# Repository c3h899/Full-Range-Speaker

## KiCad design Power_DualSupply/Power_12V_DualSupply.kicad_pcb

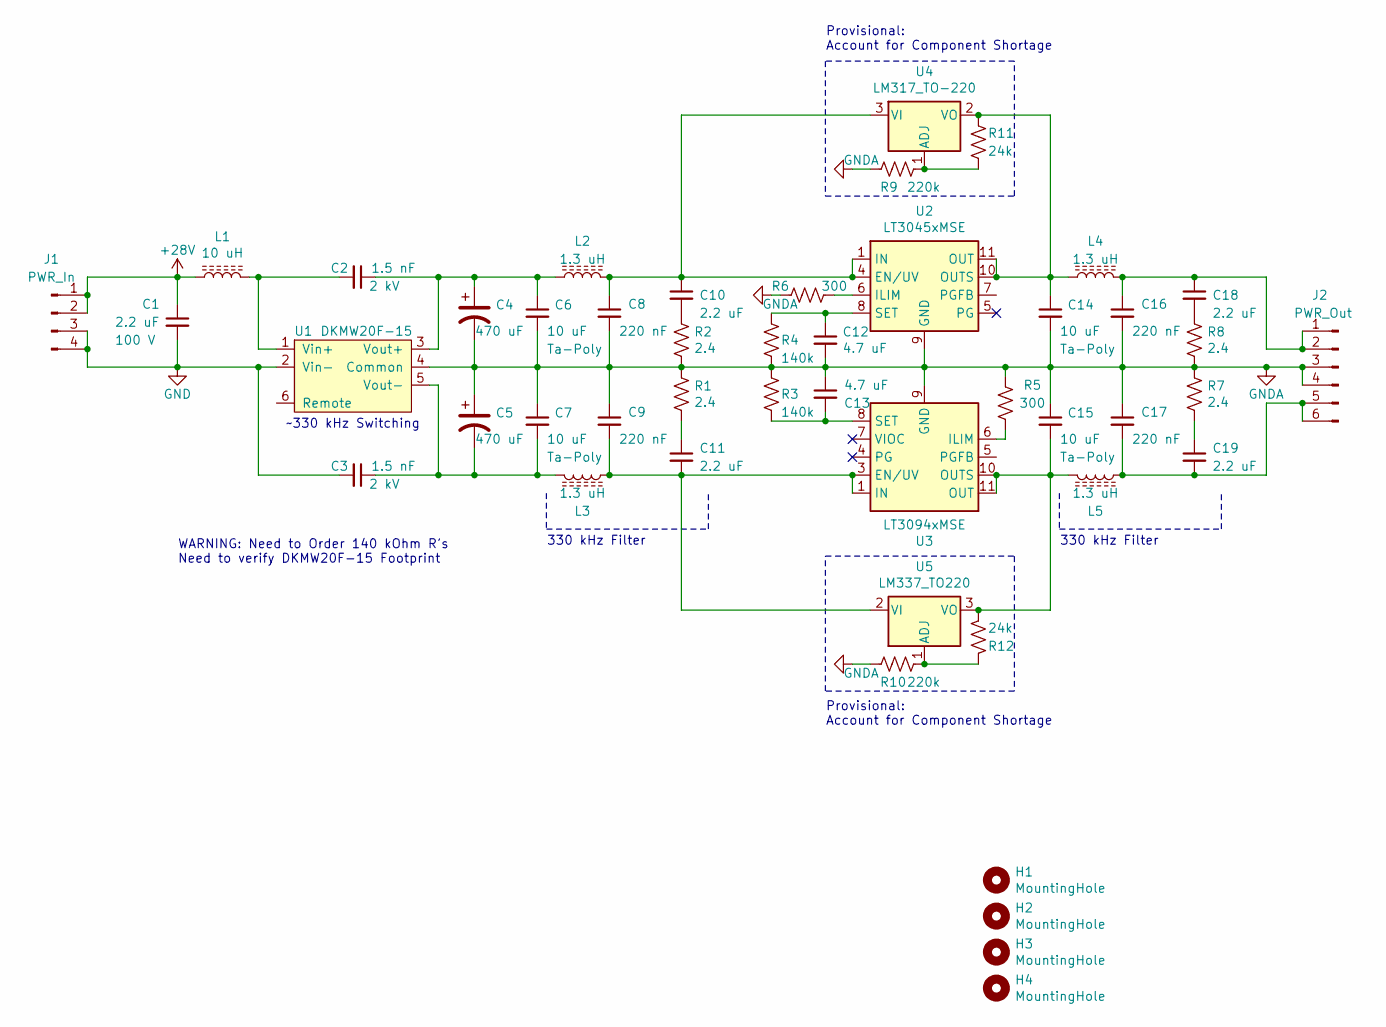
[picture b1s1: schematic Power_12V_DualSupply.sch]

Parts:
C1: 2.2 uF; C_6054; Rating 100 V; Part SMDID04220YA00KT00
C2, C3: 1.5 nF; C_1206_3216Metric_Pad1.33x1.80mm_HandSolder; Rating 2 kV; Part 1206GC152MAZ2A
C4, C5: 470 uF; CP_Radial_D10.0mm_P5.00mm; Part ESC477M035AH4AA
C6, C7, C14, C15: 10 uF; 2917_(7343_Metric)_D; Rating 50 V; Part TCJD106M050R0120
C8, C9, C16, C17: 220 nF; C_2220_5650Metric_Pad1.97x5.40mm_HandSolder; Part SMDID03220QB00MP00
C10, C11, C18, C19: 2.2 uF; C_6054; Part SMDID04220YA00KT00
C12, C13: 4.7 uF; C_1206_3216Metric_Pad1.33x1.80mm_HandSolder; Part C3216X7R1H475K160AC
H1, H2, H3, H4: MountingHole; MountingHole_3.2mm_M3_Pad_TopBottom
J1: PWR_In; PinHeader_1x04_P2.54mm_Vertical
J2: PWR_Out; PinHeader_1x06_P2.54mm_Vertical
L1: 10 uH; L_Wuerth_WE-PD-Typ-LS_Handsoldering; Part 74477110
L2, L3, L4, L5: 1.3 uH; L_Wuerth_HCM-1390; Part 7443551130
R1, R2, R7, R8: 2.4; R_2010_5025Metric_Pad1.40x2.65mm_HandSolder; Part 35022R4FT
R3, R4: 140k; C_1206_3216Metric_Pad1.33x1.80mm_HandSolder; Part RQ73C2B140KBTD
R5, R6: 300; C_1206_3216Metric_Pad1.33x1.80mm_HandSolder; Part RMCF1206FT300R
R9, R10: 220k; R_Axial_DIN0309_L9.0mm_D3.2mm_P12.70mm_Horizontal
R11, R12: 24k; R_Axial_DIN0309_L9.0mm_D3.2mm_P12.70mm_Horizontal
U1: DKMW20F-15; Converter_DCDC_MeanWell_DKMW20
U2: LT3045xMSE; MSOP-12-1EP_3x4mm_P0.65mm_EP1.65x2.85mm
U3: LT3094xMSE; MSOP-12-1EP_3x4mm_P0.65mm_EP1.65x2.85mm
U4: LM317_TO-220; TO-220-3_Vertical
U5: LM337_TO220; TO-220-3_Vertical

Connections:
+28V: C1.1, J1.1, J1.2, L1.1
GND: C1.2, C3.2, J1.3, J1.4, U1.2 (Vin-)
GNDA: C4.2, C5.1, C6.2, C7.1, C8.2, C9.1, C12.2, C13.1, C14.2, C15.1, C16.2, C17.1, J2.3, J2.4, R1.1, R2.2, R3.2, R4.1, R5.1, R6.1, R7.1, R8.2, R9.1, R10.1, U1.4 (Common), U2.9 (GND), U2.13 (GND), U3.9 (GND)
unnamed: C2.1, C4.1, C6.1, L2.1, U1.3 (Vout+)
unnamed: C2.2, L1.2, U1.1 (Vin+)
unnamed: C3.1, C5.2, C7.2, L3.2, U1.5 (Vout-)
unnamed: C8.1, C10.1, L2.2, U2.1 (IN), U2.2 (IN), U2.3 (IN), U2.4 (EN/UV), U4.3 (VI)
unnamed: C10.2, R2.1
unnamed: C11.1, R1.2
unnamed: C9.2, C11.2, L3.1, U3.1 (IN), U3.2 (IN), U3.3 (EN/UV), U3.13 (IN), U5.2 (VI)
unnamed: C12.1, R4.2, U2.8 (SET)
unnamed: C13.2, R3.1, U3.8 (SET)
unnamed: C14.1, L4.1, R11.2, U2.10 (OUTS), U2.11 (OUT), U2.12 (OUT), U4.2 (VO)
unnamed: C15.2, L5.2, R12.1, U3.10 (OUTS), U3.11 (OUT), U3.12 (OUT), U5.3 (VO)
unnamed: C16.1, C18.1, J2.1, J2.2, L4.2
unnamed: C17.2, C19.2, J2.5, J2.6, L5.1
unnamed: C18.2, R8.1
unnamed: C19.1, R7.2
unnamed: R5.2, U3.6 (ILIM)
unnamed: R6.2, U2.6 (ILIM)
unnamed: R10.2, R12.2, U5.1 (ADJ)
unnamed: R9.2, R11.1, U4.1 (ADJ)

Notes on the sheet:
~~330 kHz Switching
330 kHz Filter
WARNING: Need to Order 140 kOhm R's Need to verify DKMW20F-15 Footprint
Provisional: Account for Component Shortage

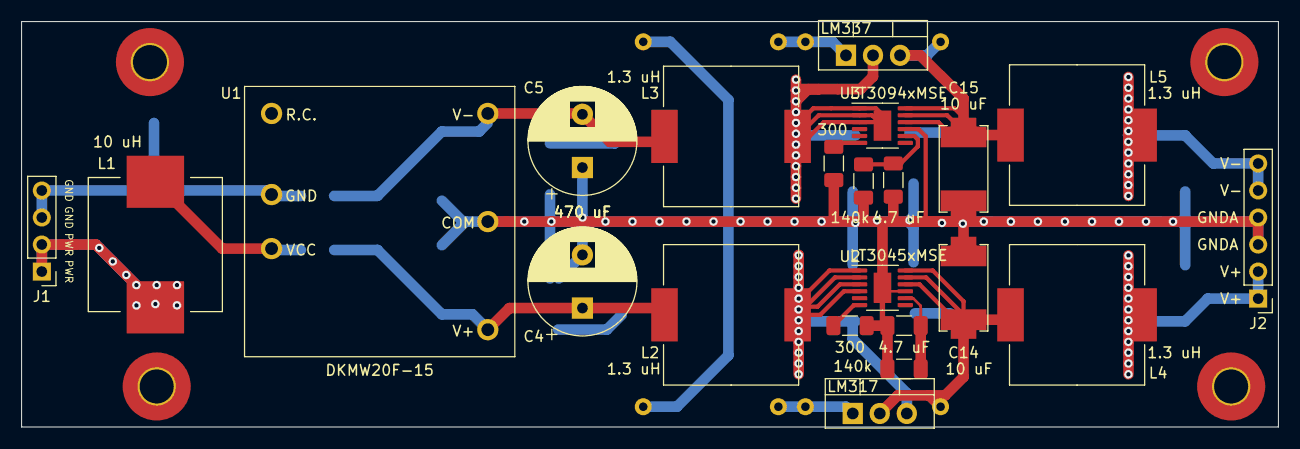
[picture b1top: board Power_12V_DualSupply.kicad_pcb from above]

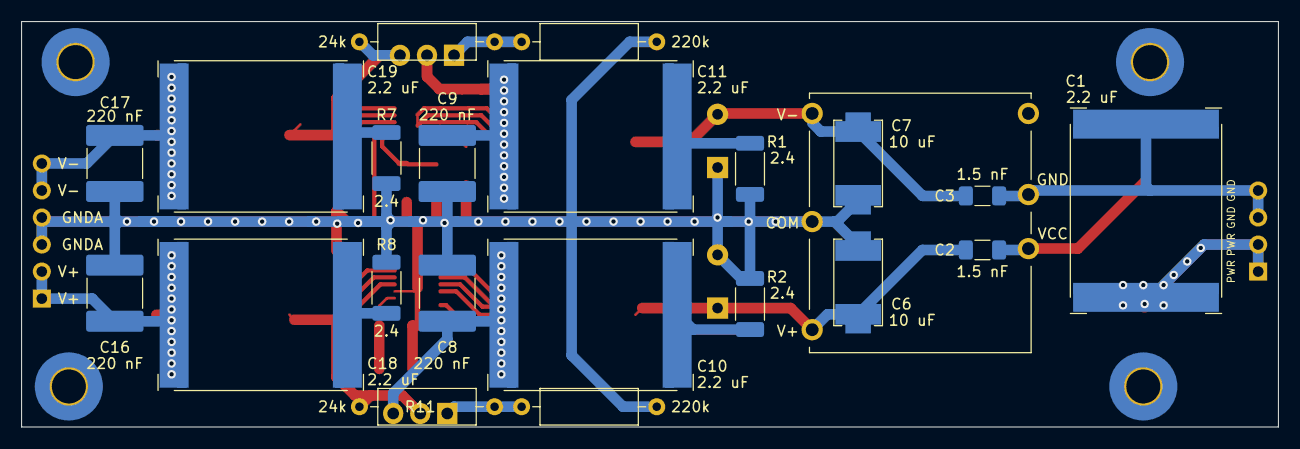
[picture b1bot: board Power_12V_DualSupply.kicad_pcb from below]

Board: 2 copper layers, 118.1 x 38.1 mm, 47 parts (21 on the bottom side), 22 nets.

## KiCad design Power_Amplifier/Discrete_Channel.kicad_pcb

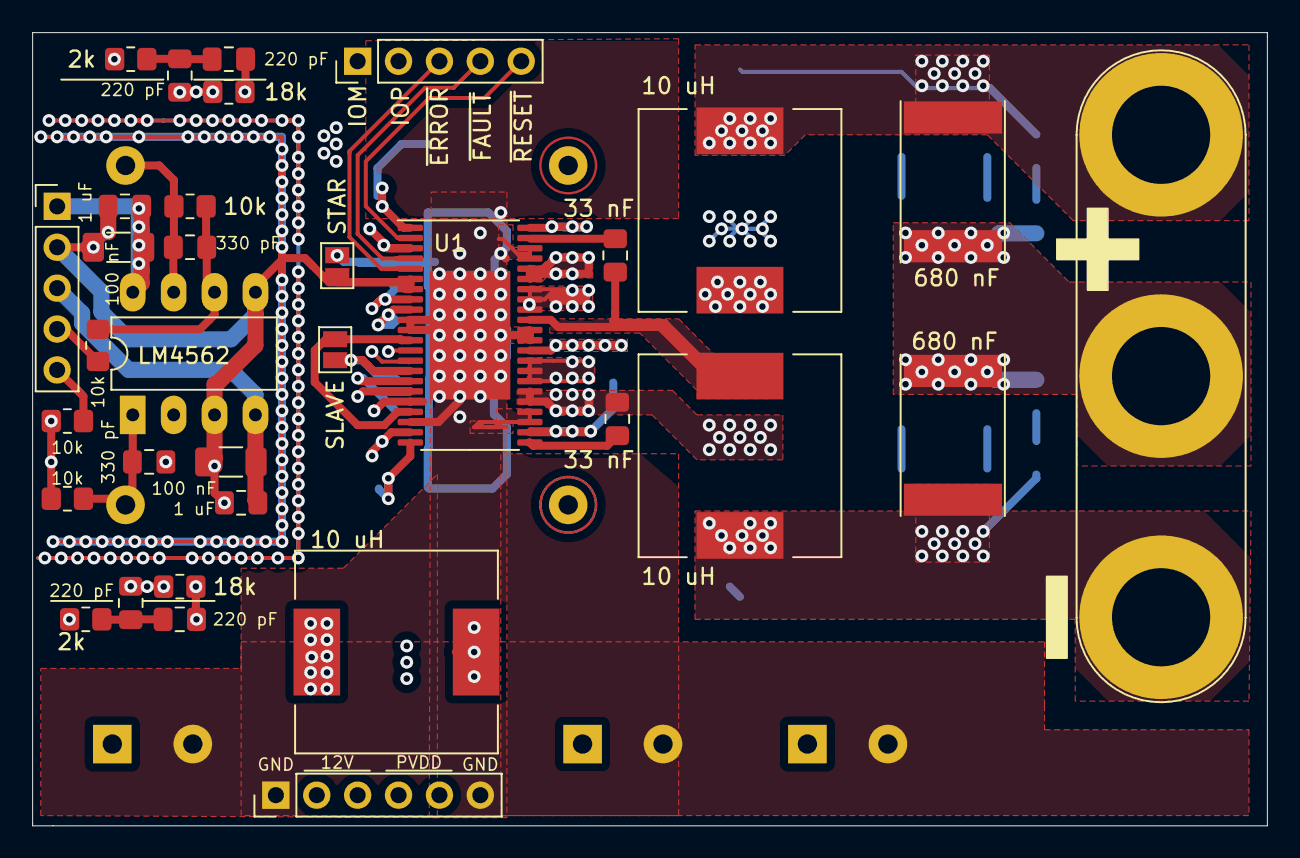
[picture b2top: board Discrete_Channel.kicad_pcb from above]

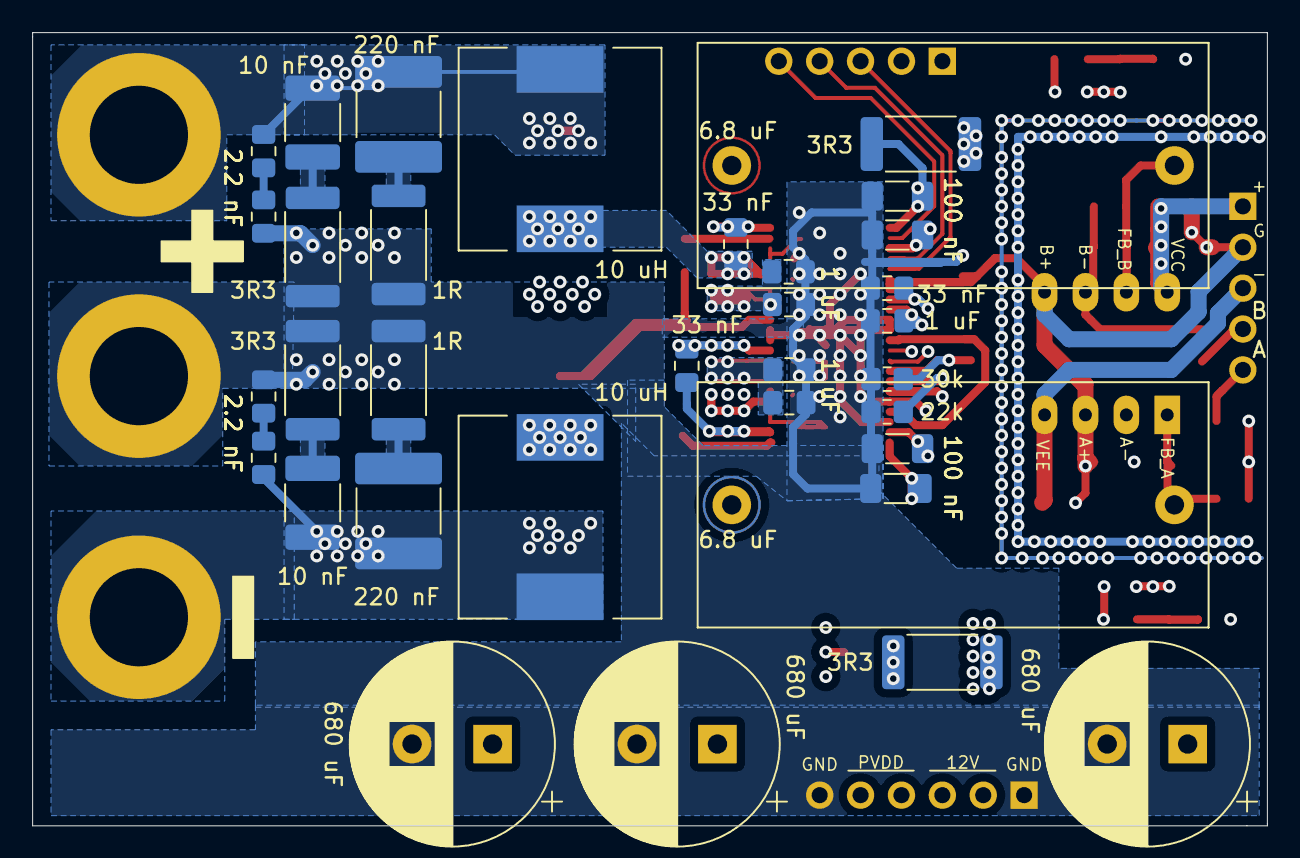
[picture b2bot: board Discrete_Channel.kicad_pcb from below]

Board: 4 copper layers, 76.7 x 49.3 mm, 68 parts (35 on the bottom side), 46 nets.

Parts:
C1, C2, C17: 680 uF; CP_Radial_D12.5mm_P5.00mm
C3, C4, C5, C7, C10, C11, C16: 1 uF; C_0805_2012Metric_Pad1.18x1.45mm_HandSolder
C6, C8, C12, C13, C14, C15: 100 nF; C_1206_3216Metric_Pad1.33x1.80mm_HandSolder
C9, C22, C23, C24, C25: 33 nF; C_0805_2012Metric_Pad1.18x1.45mm_HandSolder
C18, C19: 330 pF; C_0805_2012Metric_Pad1.18x1.45mm_HandSolder
C20, C21: 6.8 uF; C_Rect_L31.5mm_W15.0mm_P27.50mm_MKS4
C26, C27, C28, C29: 220 pF; C_0805_2012Metric_Pad1.18x1.45mm_HandSolder
C30, C31: 680 nF; C_2824
C32, C33, C34, C35: 2.2 nF; C_0805_2012Metric_Pad1.18x1.45mm_HandSolder
C36, C37: 220 nF; C_2220_5650Metric_Pad1.97x5.40mm_HandSolder
C38, C39: 10 nF; C_1812_4532Metric_Pad1.57x3.40mm_HandSolder
J1, J3: Conn_01x05_Male; PinHeader_1x05_P2.54mm_Vertical
J2: Conn_01x06_Male; PinHeader_1x06_P2.54mm_Vertical
J4: Banna Jack; Banana_Jack_3Pin
L1, L2, L3, L4, L5: 10 uH; L_12x12mm_H6mm
R1, R2, R15, R16: 3R3; R_2512_6332Metric_Pad1.40x3.35mm_HandSolder
R3: 30k; R_0805_2012Metric_Pad1.20x1.40mm_HandSolder
R4: 22k; R_0805_2012Metric_Pad1.20x1.40mm_HandSolder
R5, R6, R7, R8: 10k; R_0805_2012Metric_Pad1.20x1.40mm_HandSolder
R9, R10: 18k; R_0805_2012Metric_Pad1.20x1.40mm_HandSolder
R11, R12: 2k; R_0805_2012Metric_Pad1.20x1.40mm_HandSolder
R13, R14: 1R; R_2512_6332Metric_Pad1.40x3.35mm_HandSolder
SLAVE: Jumper_NO_Small; SolderJumper-2_P1.3mm_Open_Pad1.0x1.5mm
STAR: Star_Point; SolderJumper-2_P1.3mm_Open_Pad1.0x1.5mm
U1: TPA3244; HTSSOP-44_6.1x14mm_P0.635mm_TopEP4.14x7.01mm
U2: LM4562; DIP-8_W7.62mm_LongPads

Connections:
/+12V: C17.1, J2.2, J2.3, L1.2, R1.2, R2.2
/DVDD: SLAVE.1, U1.12, U1.19
/FB_A: C19.2, C20.2, C26.1, R8.1, R9.1, U2.1
/FB_B: C18.2, C21.2, C27.1, R7.1, R10.2, U2.7
/IN_A: J3.5, R5.2
/IN_B: J3.4, R6.2
/OSC_IOM: J1.1, U1.14
/OSC_IOP: J1.2, U1.13
/OUT_A: C22.2, L5.1, U1.27, U1.28
/OUT_B: C23.2, L2.1, U1.32
/OUT_C: C24.2, L4.1, U1.35
/OUT_D: C25.2, L3.1, U1.39, U1.40
/PVDD: C1.1, C2.1, C3.1, C4.1, C5.1, C7.1, J2.4, J2.5, U1.29, U1.30, U1.31, U1.36, U1.37, U1.38
/SPEAKER+: C28.2, C30.1, C32.1, C36.1, C38.1, J4.1, L2.2, L3.2, R9.2
/SPEAKER-: C29.2, C31.2, C35.2, C37.2, C39.2, J4.3, L4.2, L5.2, R10.1
/~ERROR: J1.5, U1.2
/~FAULT: J1.4, U1.4
/~RESET: J1.3, U1.5
GND: C1.2, C2.2, C3.2, C4.2, C5.2, C6.1, C7.2, C8.1, C9.2, C14.1, C15.1, C16.1, C17.2, C30.2, C31.1, C33.2, C34.1, J2.1, J2.6, J4.2, R3.1, R4.1, R13.2, R14.1, R15.1, R16.2, STAR.1, U1.0, U1.10, U1.11, U1.20, U1.25, U1.26, U1.33, U1.34, U1.41, U1.42
GNDA: C10.2, C11.1, C12.2, C13.1, J3.2, R11.2, R12.2, STAR.2, U1.6, U1.7, U2.3, U2.5
unnamed: C6.2, R1.1, U1.22
unnamed: C8.2, R2.1, U1.1
unnamed: C9.1, U1.8
unnamed: C14.2, L1.1, U1.21
unnamed: C15.2, U1.3
unnamed: C16.2, U1.9
unnamed: C18.1, R6.1, R7.2, U2.6
unnamed: C19.1, R5.1, R8.2, U2.2
unnamed: C20.1, U1.18
unnamed: C21.1, U1.17
unnamed: C22.1, U1.23
unnamed: C23.1, U1.24
unnamed: C24.1, U1.43
unnamed: C25.1, U1.44
unnamed: C26.2, C28.1, R11.1
unnamed: C27.2, C29.1, R12.1
unnamed: C32.2, C33.1
unnamed: C34.2, C35.1
unnamed: C36.2, R13.1
unnamed: C37.1, R14.2
unnamed: C38.2, R15.2
unnamed: C39.1, R16.1
unnamed: R3.2, SLAVE.2, U1.15
unnamed: R4.2, U1.16
VCC: C10.1, C12.1, J3.1, U2.8
VEE: C11.2, C13.2, J3.3, U2.4

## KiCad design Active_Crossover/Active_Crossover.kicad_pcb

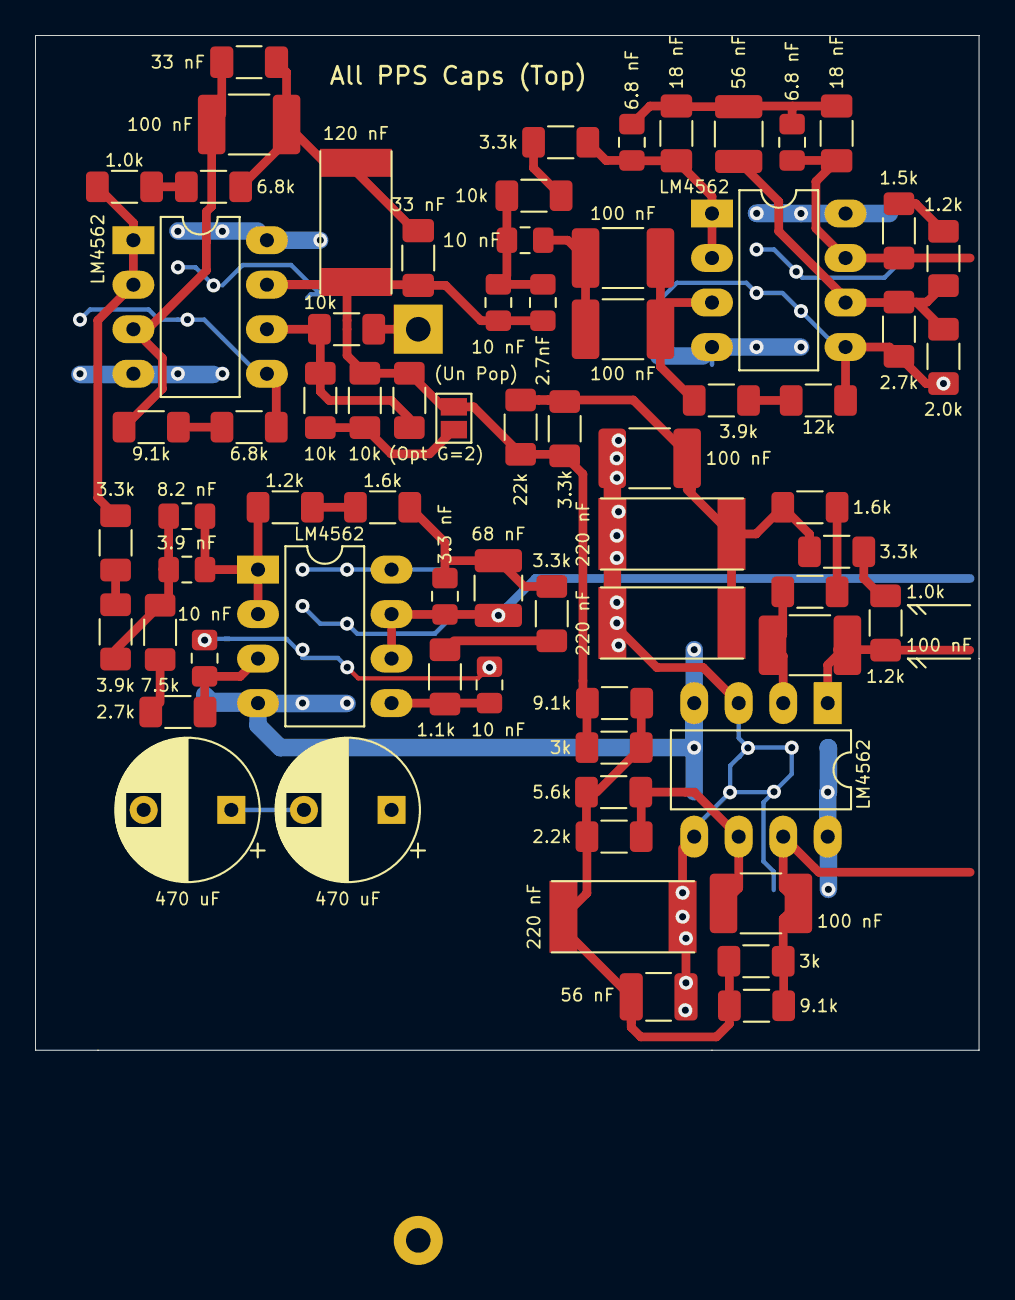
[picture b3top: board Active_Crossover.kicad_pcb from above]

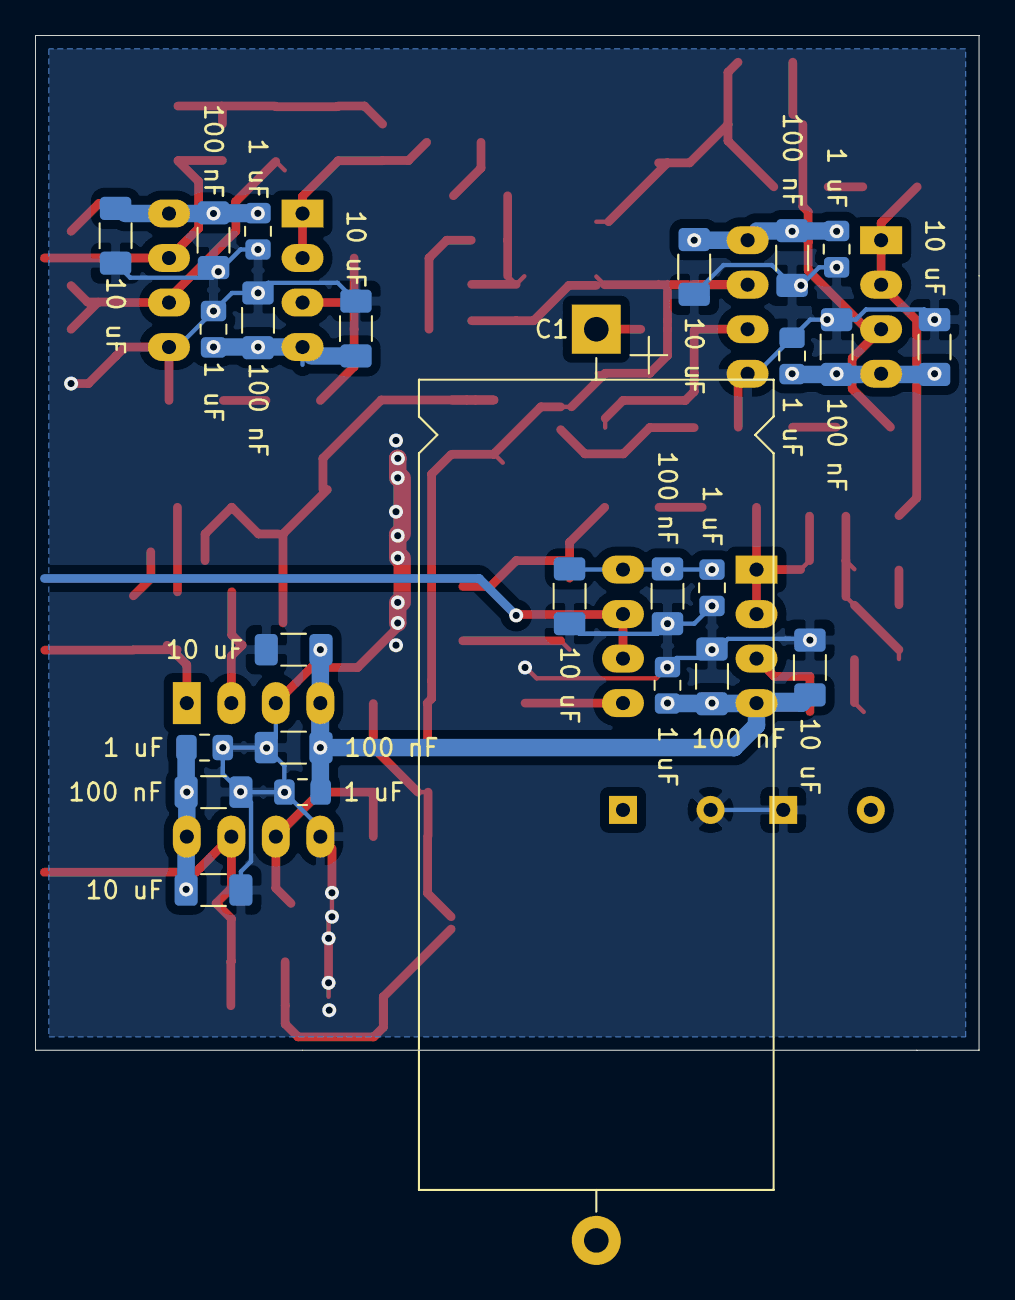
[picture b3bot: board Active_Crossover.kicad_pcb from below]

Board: 4 copper layers, 53.8 x 57.9 mm, 95 parts (25 on the bottom side), 40 nets.

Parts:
C1: 300 uF; CP_Axial_L46.0mm_D20.0mm_P52.00mm_Horizontal
C2: 120 nF; 2416_Hand_Solder
C3, C4, C6, C10: 10 nF; C_0805_2012Metric_Pad1.18x1.45mm_HandSolder
C5, C9: 33 nF; C_1206_3216Metric_Pad1.33x1.80mm_HandSolder
C7: 2.7nF; C_0805_2012Metric_Pad1.18x1.45mm_HandSolder
C8, C19, C20, C21, C22, C51: 100 nF; C_1812_4532Metric_Pad1.57x3.40mm_HandSolder
C11, C12, C13, C14, C15, C16, C17, C18: 100 nF; C_1206_3216Metric_Pad1.33x1.80mm_HandSolder
C23, C43: 18 nF; C_1206_3216Metric_Pad1.33x1.80mm_HandSolder
C24, C44: 6.8 nF; C_0805_2012Metric_Pad1.18x1.45mm_HandSolder
C25, C26, C27, C28, C29, C30, C31, C32: 1 uF; C_0805_2012Metric_Pad1.18x1.45mm_HandSolder
C33, C34, C35, C36, C37, C38, C39, C40: 10 uF; C_1206_3216Metric_Pad1.33x1.80mm_HandSolder
C41, C42: 470 uF; CP_Radial_D8.0mm_P5.00mm
C45, C52: 56 nF; C_1210_3225Metric_Pad1.33x2.70mm_HandSolder
C46: 3.9 nF; C_0805_2012Metric_Pad1.18x1.45mm_HandSolder
C47: 8.2 nF; C_0805_2012Metric_Pad1.18x1.45mm_HandSolder
C48, C49, C50: 220 nF; 2416_Hand_Solder
C53: 68 nF; C_1210_3225Metric_Pad1.33x2.70mm_HandSolder
C54: 3.3 nF; C_0805_2012Metric_Pad1.18x1.45mm_HandSolder
JP1: (Opt G=2); SolderJumper-2_P1.3mm_Open_Pad1.0x1.5mm
R1, R5: 6.8k; R_1206_3216Metric_Pad1.30x1.75mm_HandSolder
R2, R17: 3.9k; R_1206_3216Metric_Pad1.30x1.75mm_HandSolder
R3: 12k; R_1206_3216Metric_Pad1.30x1.75mm_HandSolder
R4, R26, R35: 9.1k; R_1206_3216Metric_Pad1.30x1.75mm_HandSolder
R6, R34: 1.0k; R_1206_3216Metric_Pad1.30x1.75mm_HandSolder
R7, R13, R14, R15: 10k; R_1206_3216Metric_Pad1.30x1.75mm_HandSolder
R8, R12, R24, R25, R28: 3.3k; R_1206_3216Metric_Pad1.30x1.75mm_HandSolder
R9: 2.0k; R_1206_3216Metric_Pad1.30x1.75mm_HandSolder
R10, R19: 2.7k; R_1206_3216Metric_Pad1.30x1.75mm_HandSolder
R11, R21, R33: 1.2k; R_1206_3216Metric_Pad1.30x1.75mm_HandSolder
R16: 1.5k; R_1206_3216Metric_Pad1.30x1.75mm_HandSolder
R18: 7.5k; R_1206_3216Metric_Pad1.30x1.75mm_HandSolder
R20: (Un Pop); R_1206_3216Metric_Pad1.30x1.75mm_HandSolder
R22, R29: 1.6k; R_1206_3216Metric_Pad1.30x1.75mm_HandSolder
R23: 22k; R_1206_3216Metric_Pad1.30x1.75mm_HandSolder
R27, R36: 3k; R_1206_3216Metric_Pad1.30x1.75mm_HandSolder
R30: 1.1k; R_1206_3216Metric_Pad1.30x1.75mm_HandSolder
R31: 5.6k; R_1206_3216Metric_Pad1.30x1.75mm_HandSolder
R32: 2.2k; R_1206_3216Metric_Pad1.30x1.75mm_HandSolder
U1, U2, U3, U4: LM4562; DIP-8_W7.62mm_LongPads

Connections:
/LFE_Out: C20.1, R35.1, R36.1, U4.7
/Mid_Out: C53.1, C54.1, U3.6, U3.7
/Subwoofer_Out: C19.1, R33.2, U4.1
/Tweeter_Out: C43.1, C44.1, R16.2, U2.7
/VCC: C11.1, C13.1, C15.1, C17.1, C25.1, C27.1, C29.1, C31.1, C33.1, C35.1, C37.1, C39.1, C41.1, U1.8, U2.8, U3.8, U4.8
/VEE: C12.2, C14.2, C16.2, C18.2, C26.2, C28.2, C30.2, C32.2, C34.2, C36.2, C38.2, C40.2, C42.2, U1.4, U2.4, U3.4, U4.4
/~Signal: C2.2, C5.2, C6.2, C7.2, JP1.2, R15.2, R20.1, R23.2, R24.2, R26.2, R27.2, U1.7
GNDA: C3.2, C4.2, C11.2, C12.1, C13.2, C14.1, C15.2, C16.1, C17.2, C18.1, C25.2, C26.1, C27.2, C28.1, C29.2, C30.1, C31.2, C32.1, C33.2, C34.1, C35.2, C36.1, C37.2, C38.1, C39.2, C40.1, C41.2, C42.1, C48.2, C49.2, C50.2, C51.1, C52.2, R3.1, R5.1, R9.1, R10.1, U1.5, U2.5, U4.3, U4.5
unnamed: C1.1, R13.1
unnamed: C2.1, C5.1, C8.2, C9.2, R1.2
unnamed: C3.1, R19.2, U3.3
unnamed: C4.1, R30.2, U3.5
unnamed: C8.1, C9.1, R4.2, U1.3
unnamed: C10.1, C21.2, C22.2
unnamed: C6.1, C7.1, C10.2, R7.1
unnamed: C19.2, R34.2, U4.2
unnamed: C20.2, R31.1, R32.1, U4.6
unnamed: C21.1, C22.1, R2.2, U2.3
unnamed: C23.1, C24.1, C43.2, C44.2, C45.1
unnamed: C23.2, C24.2, R8.2, U2.1, U2.2
unnamed: C45.2, R9.2, R10.2, R11.1, U2.6
unnamed: C46.1, C47.1, R21.1, U3.1, U3.2
unnamed: C46.2, C47.2, R17.2, R18.1
unnamed: C48.1, C49.1, C51.2, R23.1, R24.1, R28.1, R29.1
unnamed: C50.1, C52.1, R26.1, R27.1, R31.2, R32.2, R35.2, R36.2
unnamed: C53.2, C54.2, R22.2, R25.1
unnamed: JP1.1, R14.1, R15.1
unnamed: R1.1, R6.2
unnamed: R2.1, R3.2
unnamed: R4.1, R5.2
unnamed: R7.2, R8.1
unnamed: R11.2, R16.1
unnamed: R6.1, R12.1, U1.1, U1.2
unnamed: R12.2, R17.1
unnamed: R13.2, R14.2, R20.2, U1.6
unnamed: R18.2, R19.1
unnamed: R21.2, R22.1
unnamed: R25.2, R30.1
unnamed: R28.2, R33.1
unnamed: R29.2, R34.1

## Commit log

2021-11-07 Add files via upload
    Measurements
2021-11-26 Initial Measurement / Calibration with Cabinet
2021-11-26 Comparison of Desired and Measured Reponse
    Single chamber for both mid-bass and sub. Modeling the mid-bass as a 2nd passive radiator in parallel with the intended reveals the low frequency cut-off response measured.
2021-11-27 Rename Speaker Measurements (DATS V3)/Dual Coil Sub (SD270A-88, Series).txt to Speaker Measurements (DATS V3)/Free Space/Dual Coil Sub (SD270A-88, Series).txt
2021-11-27 Rename Speaker Measurements (DATS V3)/Dual Coil Sub_Loaded_InSitu (SD270A-88, Series).txt to Speaker Measurements (DATS V3)/Free Space/Dual Coil Sub_Loaded_InSitu (SD270A-88, Series).txt
2021-11-27 Rename Speaker Measurements (DATS V3)/Mid (HiVi F8).txt to Speaker Measurements (DATS V3)/Free Space/Mid (HiVi F8).txt
2021-11-27 Rename Speaker Measurements (DATS V3)/Single Coil Sub (SD270A-88, Floating 2nd Coil).txt to Speaker Measurements (DATS V3)/Free Space/Single Coil Sub (SD270A-88, Floating 2nd Coil).txt
2021-12-04 Theoretical Design
    Passive Filter derived from mild optimization and component rejection for a 2nd-order Bessel response with (f1 = 200 Hz) and (f2 = 2000 Hz)
2022-01-02 Circuit R2
    Fixed Issue with heatsink pad shorting out amplifier.
2022-01-11 Added LFE Out on Channel 4
    LFE output included on channel 4 for use with separate powered subwoofer.
2022-01-15 Transitioning Report to LaTeX
2022-01-16 Renamed Directory
    Discrete_Channel --> Power_Amplifier
    Additional work done to report.
    Invoices Added.
2022-01-16 Initial Upload
    Initial Upload of Ongoing Efforts
2022-01-18 Cleared Temp Files
    Adding gitignore
2022-11-09 WiP - Schematic Edits
    Fixed Zobel Network
    Adopted TPA3245
    TODO: Revise PCB
2023-10-04 Add files via upload
    LatestRevision
